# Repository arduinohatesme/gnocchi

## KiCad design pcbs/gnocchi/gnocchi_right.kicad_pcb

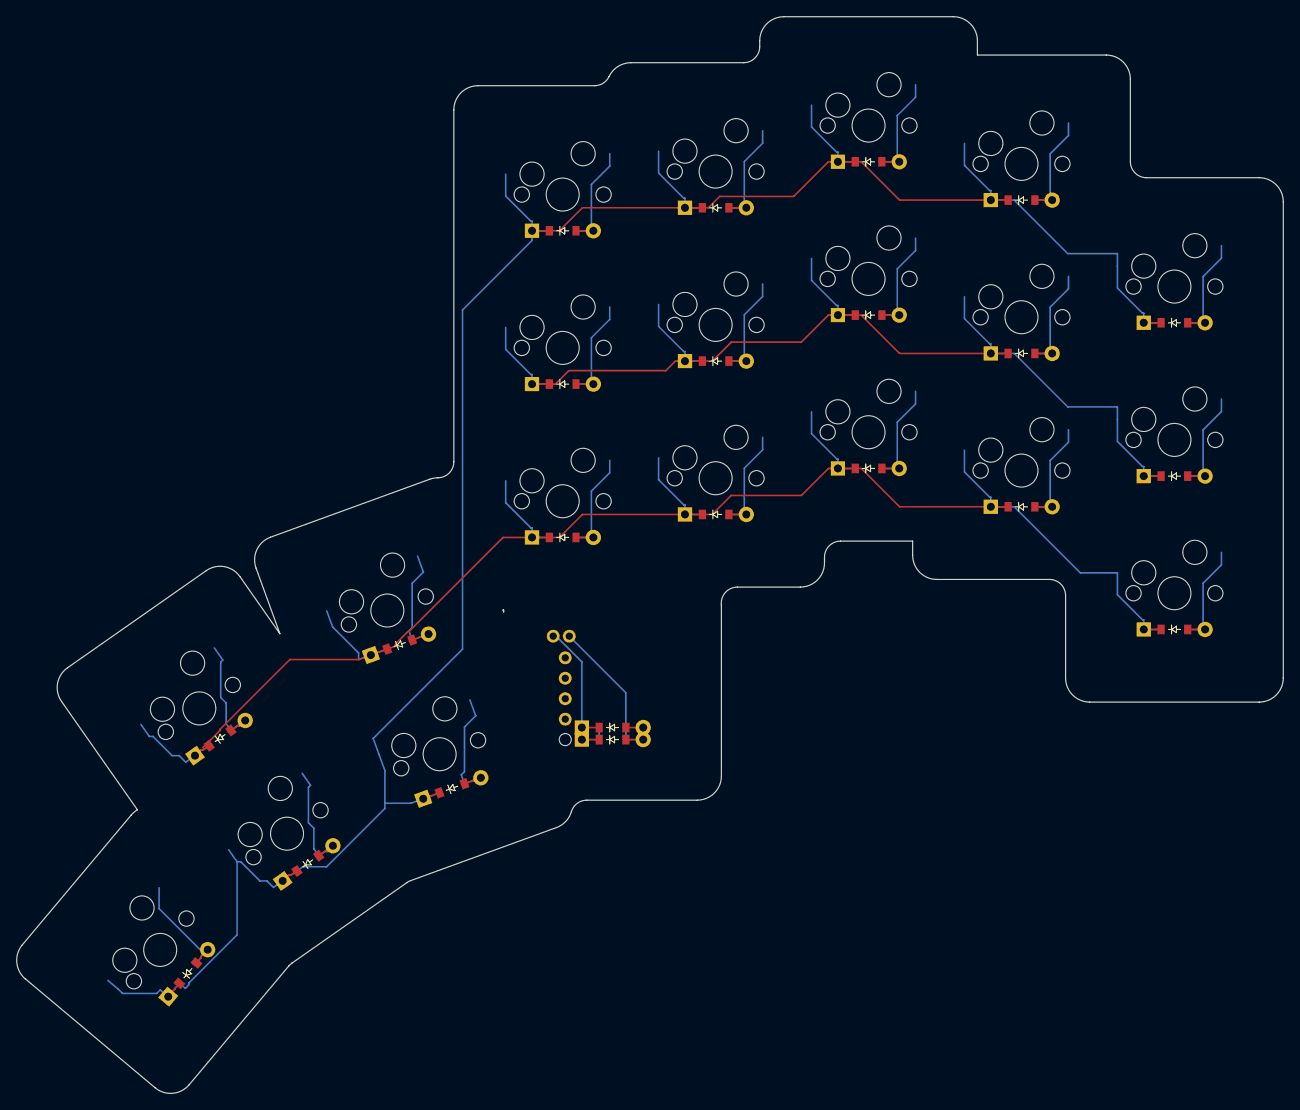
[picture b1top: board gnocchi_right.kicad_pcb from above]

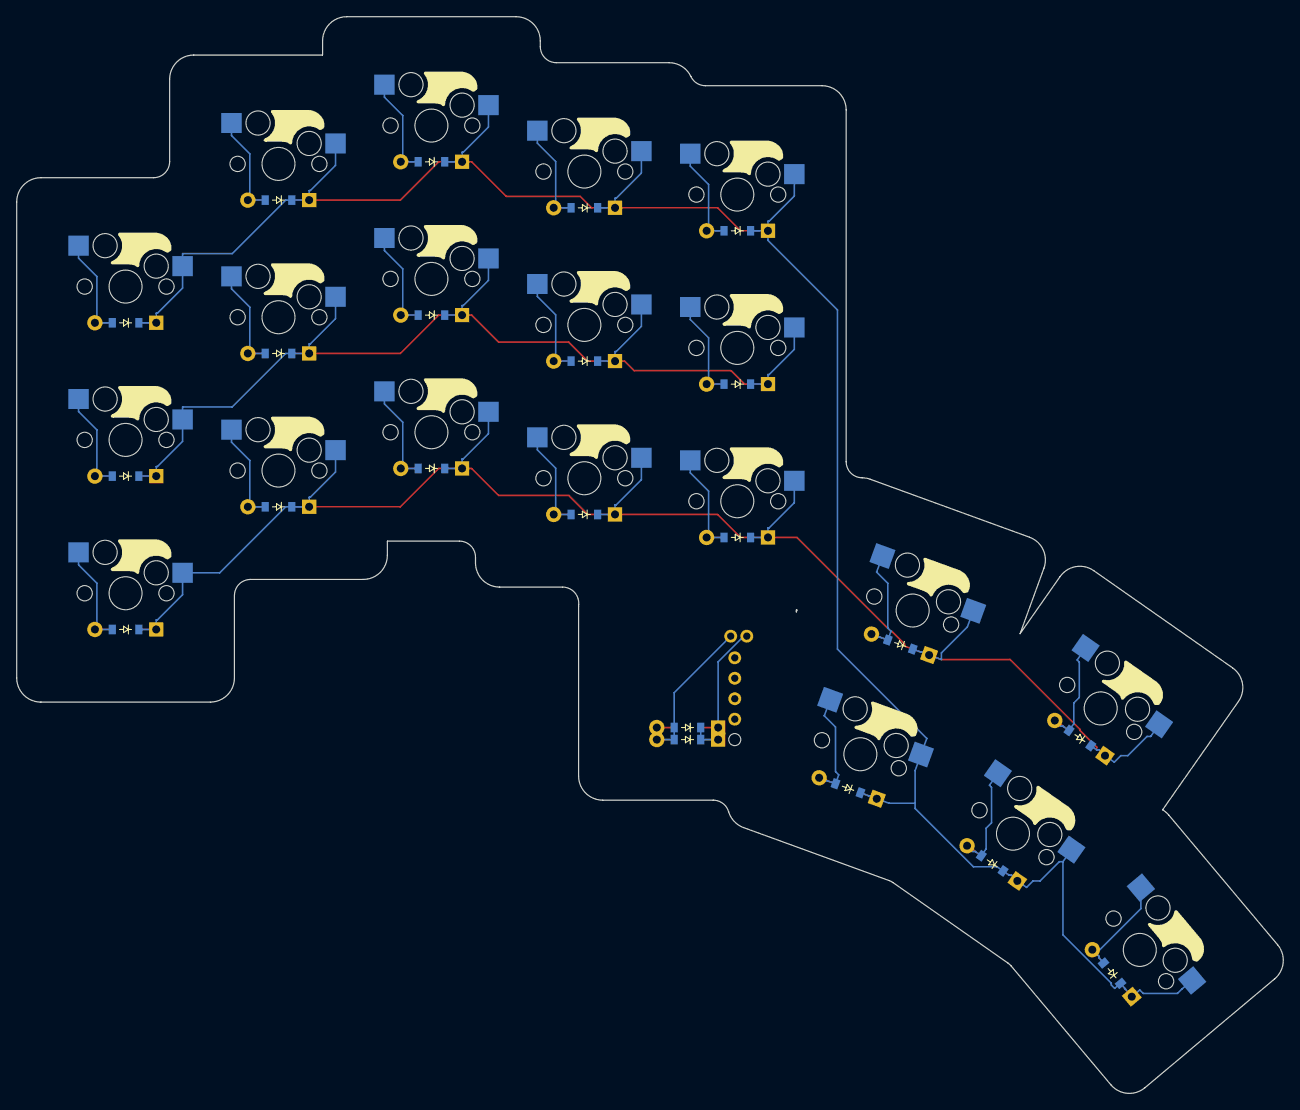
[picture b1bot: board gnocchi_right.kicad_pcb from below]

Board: 2 copper layers, 157.4 x 133.8 mm, 42 parts (20 on the bottom side), 25 nets.

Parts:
D1, D2, D3, D4, D5, D6, D7, D8, D9, D10, D11, D12, D13, D14, D15, D16, D17, D18, D19, D20, D21, D22: ComboDiode
S1, S2, S3, S4, S5, S6, S7, S8, S9, S10, S11, S12, S13, S14, S15, S16, S17, S18, S19, S20: switch_mx

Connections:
bottom: D2.1, D5.1, D8.1, D11.1, D14.1, D18.1, D20.1, S1.1, S4.1, S7.1, S10.1, S13.1, S17.1, S19.1
default: D1.1, D22.1
home: D3.1, D6.1, D9.1, D12.1, D15.1, S2.1, S5.1, S8.1, S11.1, S14.1
mirror_index_bottom: D11.2, S10.2
mirror_index_home: D12.2, S11.2
mirror_index_top: D13.2, S12.2
mirror_inner_bottom: D14.2, S13.2
mirror_inner_home: D15.2, S14.2
mirror_inner_top: D16.2, S15.2
mirror_main_default: D1.2, D22.2
mirror_mid_bottom: D20.2, S19.2
mirror_mid_top: D19.2, S18.2
mirror_middle_bottom: D8.2, S7.2
mirror_middle_home: D9.2, S8.2
mirror_middle_top: D10.2, S9.2
mirror_pinky_bottom: D2.2, S1.2
mirror_pinky_home: D3.2, S2.2
mirror_pinky_top: D4.2, S3.2
mirror_reachy_top: D21.2, S20.2
mirror_ring_bottom: D5.2, S4.2
mirror_ring_home: D6.2, S5.2
mirror_ring_top: D7.2, S6.2
mirror_tucky_bottom: D18.2, S17.2
mirror_tucky_top: D17.2, S16.2
top: D4.1, D7.1, D10.1, D13.1, D16.1, D17.1, D19.1, D21.1, S3.1, S6.1, S9.1, S12.1, S15.1, S16.1, S18.1, S20.1

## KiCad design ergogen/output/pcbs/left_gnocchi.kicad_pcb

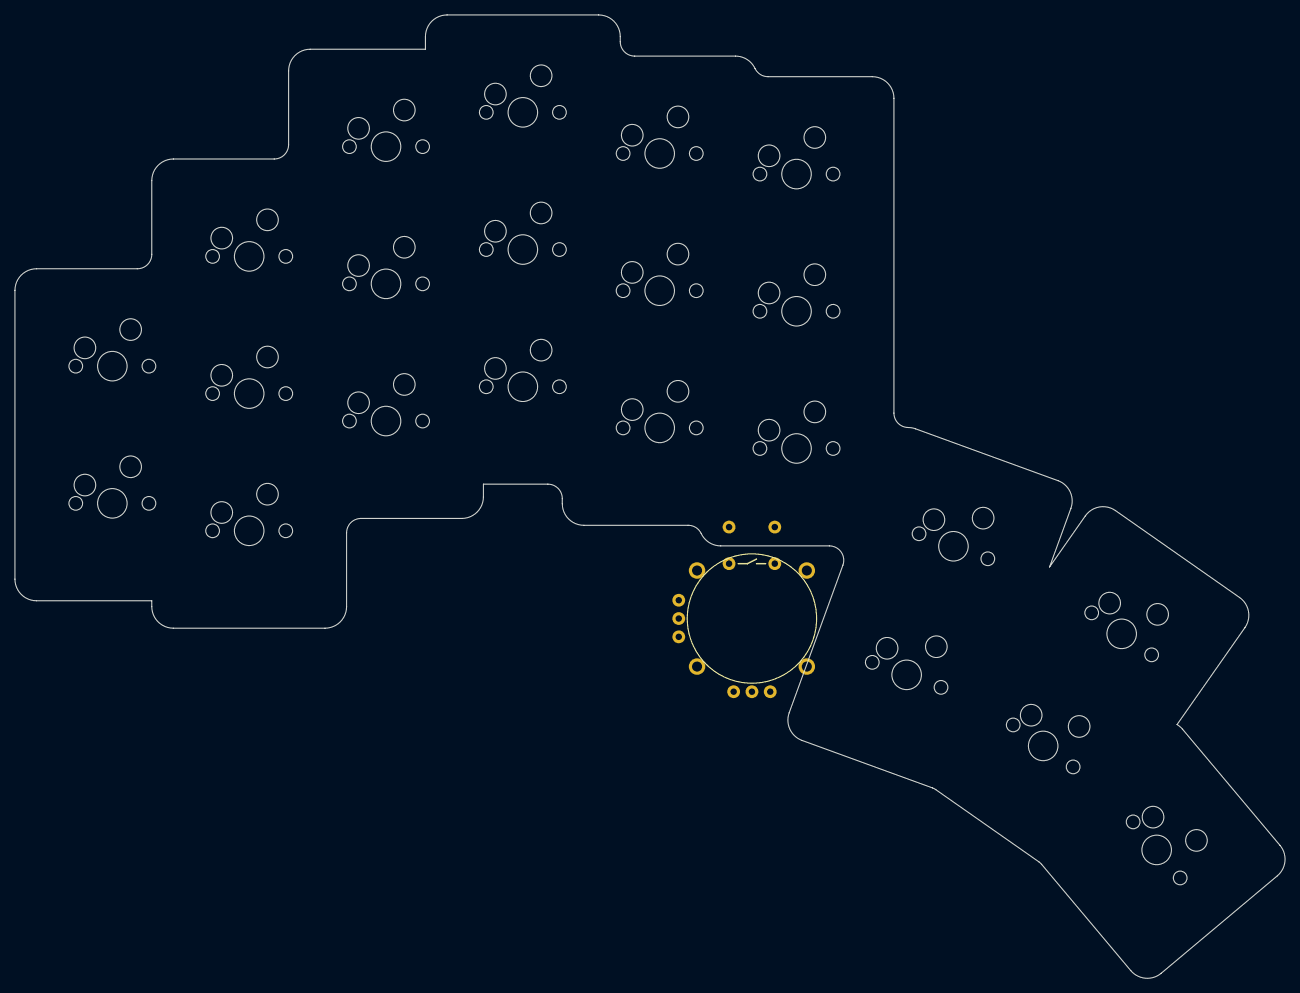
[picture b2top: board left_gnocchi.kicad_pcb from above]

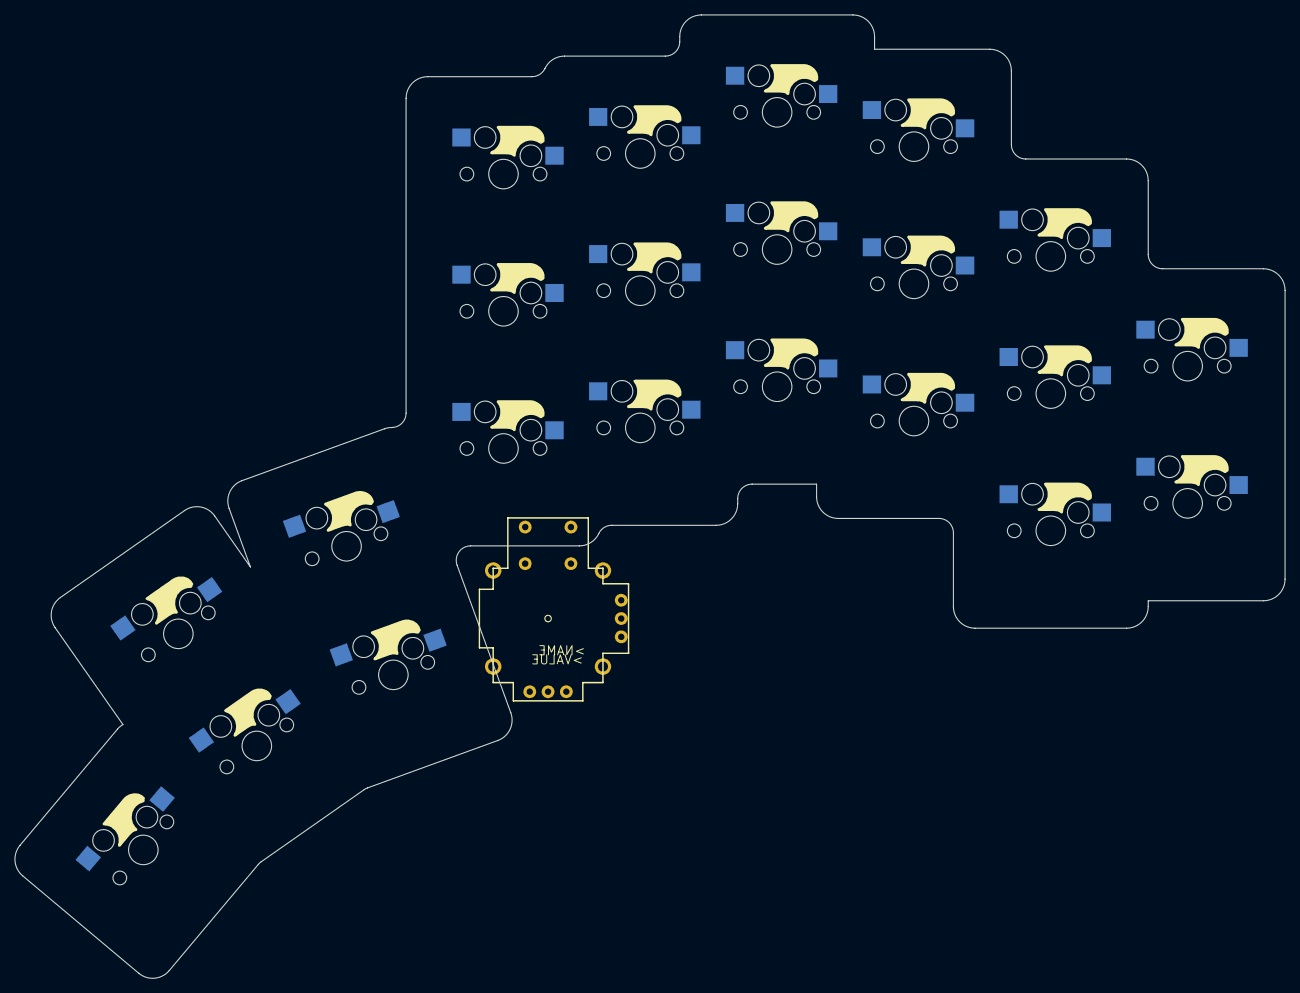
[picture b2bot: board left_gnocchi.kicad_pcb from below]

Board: 2 copper layers, 176.4 x 133.8 mm, 23 parts (22 on the bottom side), 10 nets, no tracks yet.

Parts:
J1: JOYSTICK
S1, S2, S3, S4, S5, S6, S7, S8, S9, S10, S11, S12, S13, S14, S15, S16, S17, S18, S19, S20, S21, S22: switch_mx

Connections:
GND: J1.B1B, J1.B2A, J1.B2B, J1.H1, J1.MOUN, J1.V1
P009: S9.1, S10.1, S11.1
P010: S6.1, S7.1, S8.1
P104: S15.1, S16.1, S17.1
P106: S12.1, S13.1, S14.1
P111: S3.1, S4.1, S5.1
P113: S1.1, S2.1
VCC: J1.H3, J1.V3
middle_bottom: S9.2, S21.2
middle_top: S11.2, S20.2

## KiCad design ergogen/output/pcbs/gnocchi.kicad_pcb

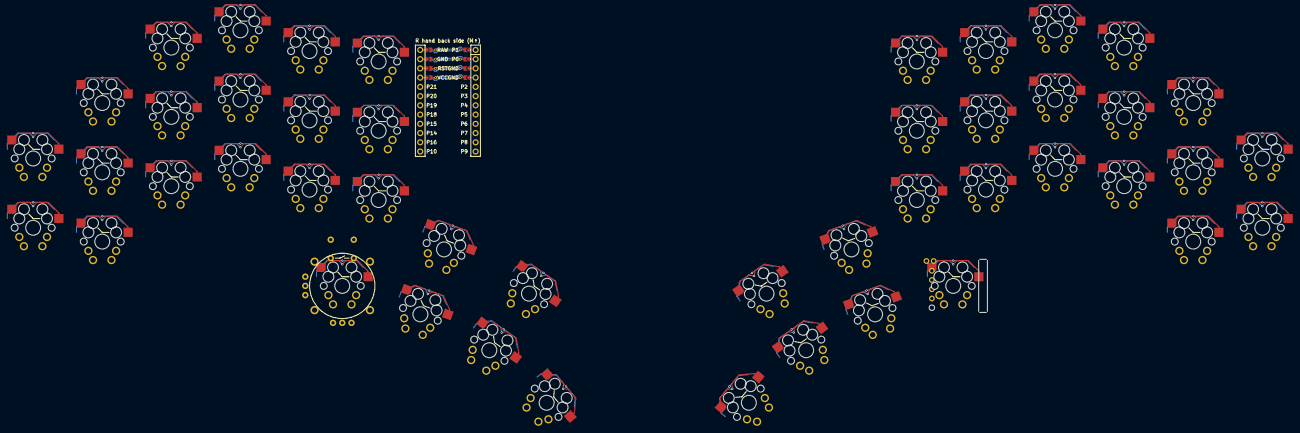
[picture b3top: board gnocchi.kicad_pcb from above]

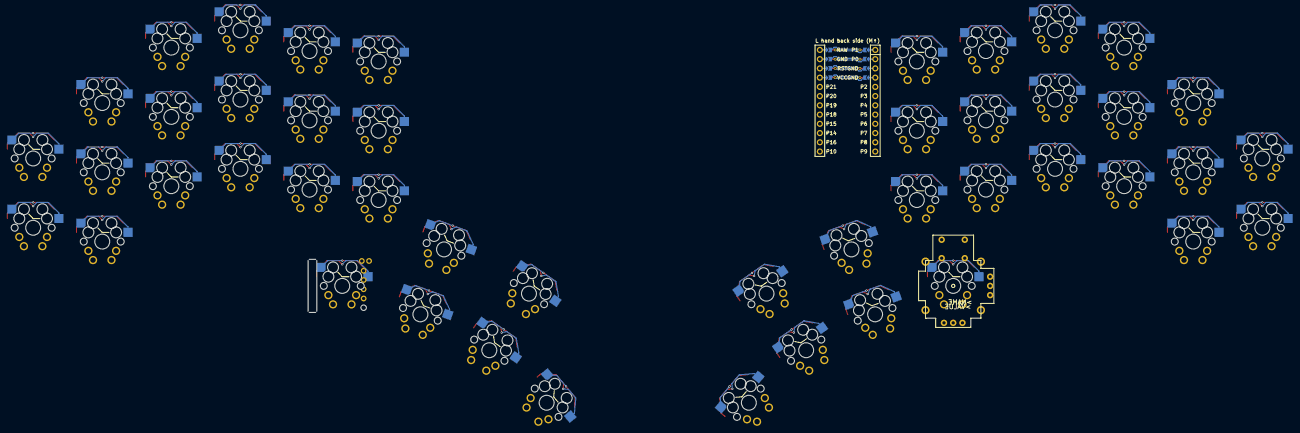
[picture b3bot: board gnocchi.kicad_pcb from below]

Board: 2 copper layers, 48 parts (46 on the bottom side), 17 nets.

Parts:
J1: JOYSTICK
MCU1: mcu_nice_nano
S1, S2, S3, S4, S5, S6, S7, S8, S9, S10, S11, S12, S13, S14, S15, S16, S17, S18, S19, S20, S21, S22, S23, S24, S25, S26, S27, S28, S29, S30, S31, S32, S33, S34, S35, S36, S37, S38, S39, S40, S41, S42, S43, S44, S45, S46: switch_mx

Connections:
GND: J1.B1B, J1.B2A, J1.B2B, J1.H1, J1.MOUN, J1.V1, MCU1.103, MCU1.104, MCU1.123, S1.1, S2.1, S3.1, S4.1, S5.1, S6.1, S7.1, S8.1, S9.1, S10.1, S11.1, S12.1, S13.1, S14.1, S15.1, S16.1, S17.1, S18.1, S19.1, S20.1, S21.1, S22.1, S23.1, S24.1, S25.1, S26.1, S27.1, S28.1, S29.1, S30.1, S31.1, S32.1, S33.1, S34.1, S35.1, S36.1, S37.1, S38.1, S39.1, S40.1, S41.1, S42.1, S43.1, S44.1, S45.1, S46.1
VCC: J1.H3, J1.V3, MCU1.121
matrix_index_bottom: MCU1.8, S12.2
matrix_index_home: MCU1.13, S13.2
matrix_index_top: MCU1.19, S14.2
matrix_inner_bottom: MCU1.9, S15.2
matrix_inner_home: MCU1.101, S16.2
matrix_inner_top: MCU1.20, S17.2
matrix_middle_bottom: MCU1.7, S9.2
matrix_middle_home: MCU1.14, S10.2
matrix_middle_top: MCU1.18, S11.2
matrix_pinky_bottom: MCU1.5, S3.2
matrix_pinky_home: MCU1.16, S4.2
matrix_pinky_top: MCU1.10, S5.2
matrix_ring_bottom: MCU1.6, S6.2
matrix_ring_home: MCU1.15, S7.2
matrix_ring_top: MCU1.17, S8.2

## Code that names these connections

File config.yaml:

meta:
  engine: 4.1.0
# U is a predefined unit of measure that means 19.05mm, which is MX spacing (u is 19.00mm)
points:
  zones:
    matrix:
      anchor.shift: [50,-100] # Fix KiCad placement
      columns:
        xtra_pinky:
          rows:
            top:
              skip: true
        pinky.key.stagger: -0.2U
        ring.key.stagger: 0.66U
        middle.key.stagger: 0.25U
        index.key.stagger: -0.25U
        inner.key.stagger: -0.15U
      rows:
        bottom.padding: U
        home.padding: U
        top.padding: U
    thumb:
      anchor:
        ref: matrix_index_bottom
        shift: [1.6U, -2U]
      columns:
        tucky:
          key.splay: -20
          rows:
            top:
              key.name: thumb_tucky_high
            bottom:
              key.name: thumb_tucky_low
        middle:
          key.spread: U
          key.splay: -15
          key.origin: [-0.5U, -0.5U]
          rows:
            top:
              key.name: thumb_middle_high
            bottom:
              key.name: thumb_middle_low
        reachy:
          key.spread: U
          key.splay: -15
          key.origin: [-0.5U, -0.5U]
          rows:
            top:
              key.name: thumb_reachy_low
            bottom:
              skip: true

pcbs:
  simple_split:
    template: kicad8
    footprints:
      keys:
        what: ceoloide/switch_mx
        where: true
        params:
          from: GND
          to: "{{name}}"
          reversible: true
          solder: true
          include_keycap: true
      mcu:
        what: ceoloide/mcu_nice_nano
        where:
          - ref: matrix_inner_home
            shift: [1U, 0.5U]
        params:
          reversible: true
          only_required_jumpers: true
          P7: matrix_pinky_top
          P7_label: P7
          P18: matrix_ring_top
          P18_label: P18
          P19: matrix_middle_top
          P19_label: P19
          P20: matrix_index_top
          P20_label: P20
          P21: matrix_inner_top
          P21_label: P21
          P15: matrix_pinky_home
          P15_label: P15
          P14: matrix_ring_home
          P14_label: P14
          P16: matrix_middle_home
          P16_label: P16
          P10: matrix_index_home
          P10_label: P10
          P1: matrix_inner_home
          P1_label: P1
          P2: matrix_pinky_bottom
          P2_label: P2
          P3: matrix_ring_bottom
          P3_label: P3
          P4: matrix_middle_bottom
          P4_label: P4
          P5: matrix_index_bottom
          P5_label: P5
          P6: matrix_inner_bottom
          P6_label: P6
          P8: thumb_tucky
          P8_label: P8
          P9: thumb_reachy
          P9_label: P9

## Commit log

2026-06-26 Add configuration for PCB and key layout
2026-06-26 Refactor key configuration in config.yaml
2026-06-26 Update config, add joystick (PCB OUTDATED)
2026-06-26 Add shell.nix, include ceoloide, add scroll wheel
2026-06-27 Fix up kicad pcb
2026-06-27 Make wheel work (need to find a better way to map keys)
2026-06-28 Progress on outlines
2026-06-28 MADE THE ZIP FILE
